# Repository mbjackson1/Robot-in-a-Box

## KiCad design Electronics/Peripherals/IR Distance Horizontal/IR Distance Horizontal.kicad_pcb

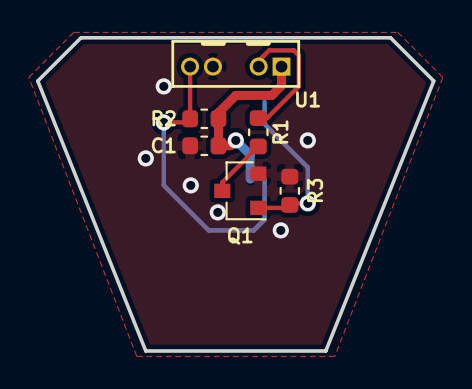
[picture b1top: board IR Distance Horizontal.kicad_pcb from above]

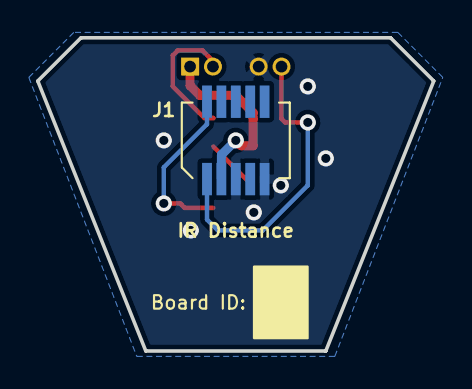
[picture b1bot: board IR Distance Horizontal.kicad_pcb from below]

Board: 2 copper layers, 22.0 x 17.4 mm, 9 parts (2 on the bottom side), 6 nets.

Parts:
C1: 100nF; C_0603_1608Metric
J1: Conn_01x10; Molex_SlimStack_533071071_2x05_P0.8mm_Vertical_Female
Q1: FDV303N; SOT-23
R1: 22R; R_0603_1608Metric
R2, R3: 10k; R_0603_1608Metric
T1: IR Distance; PCB_Title_&_Version
T2: Board ID; Board_Number
U1: TCRT1000; Vishay_TCRT10x0_Reflective_Sensor

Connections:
+3V3: C1.2, J1.3, R2.1, U1.1
/ANALOG: J1.1, R2.2, U1.4
/TIMER: J1.2, Q1.1, R3.2
GND: C1.1, J1.5, J1.9, Q1.2, R3.1, U1.3
unnamed: Q1.3, R1.1
unnamed: R1.2, U1.2

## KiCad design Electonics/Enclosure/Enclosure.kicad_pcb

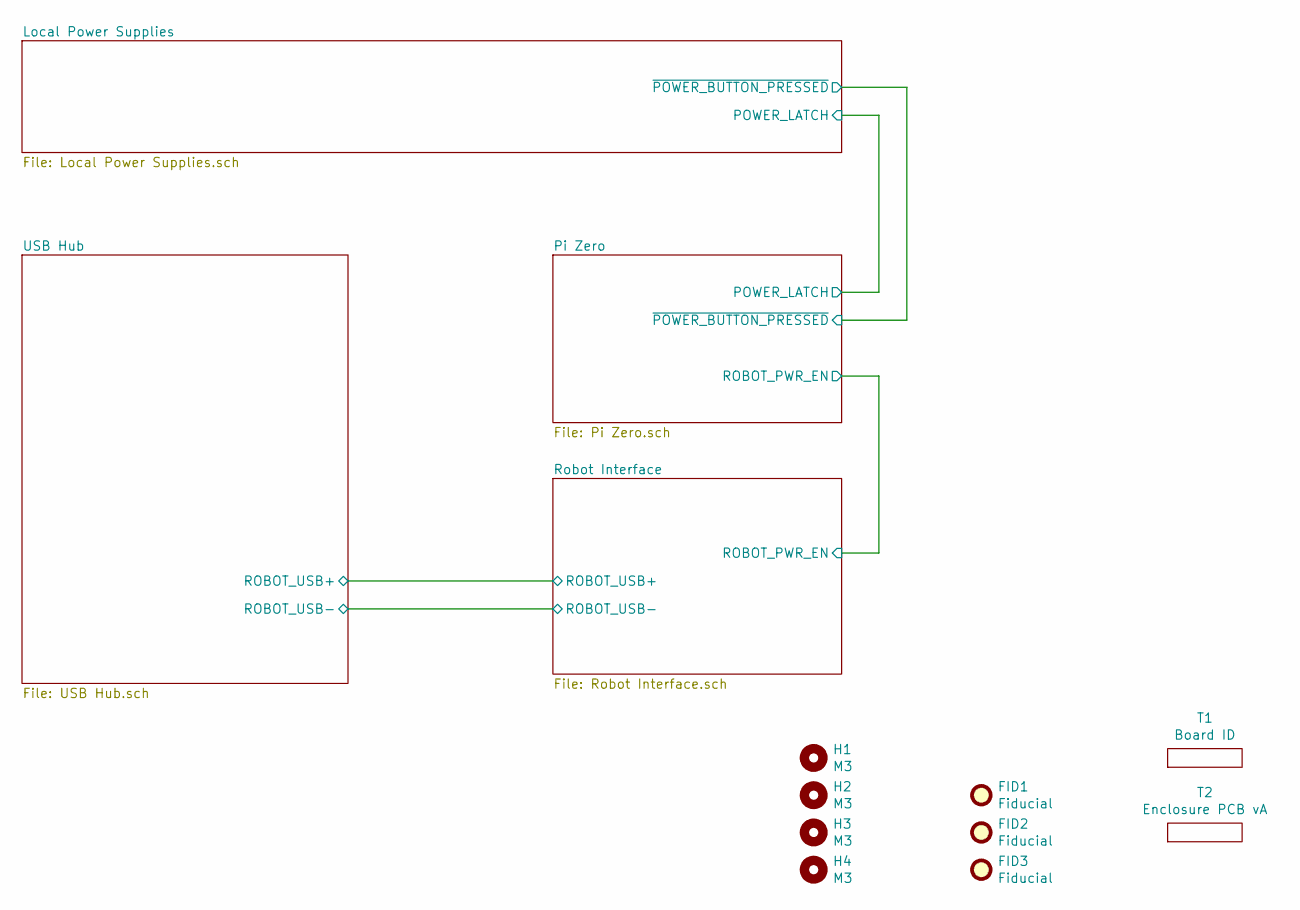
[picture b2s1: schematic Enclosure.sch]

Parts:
FID1, FID2, FID3: Fiducial; Fiducial_0.5mm_Mask1mm
H1, H2, H3, H4: M3; MountingHole_3.2mm_M3
T1: Board ID; Board_Number
T2: Enclosure PCB vA; PCB_Title_&_Version

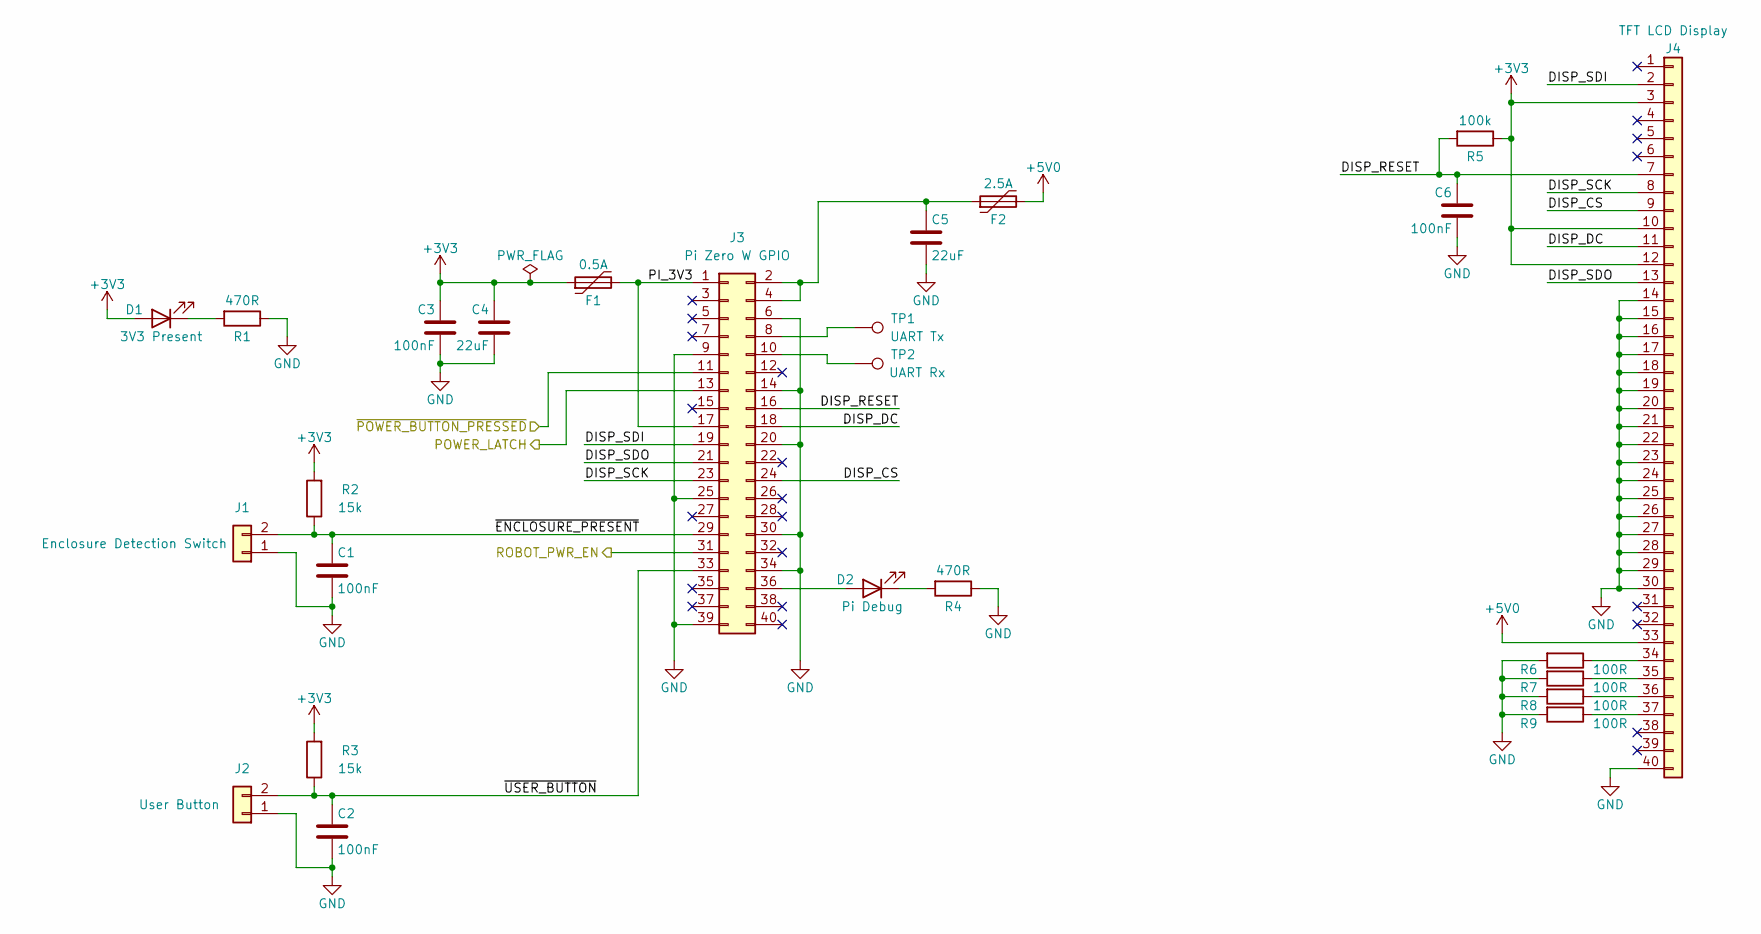
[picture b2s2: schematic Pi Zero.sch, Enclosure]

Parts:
C1, C2, C3, C6: 100nF; C_0603_1608Metric; Manufacturer Part Number CL10B104KB8NNNL; LCSC Part Number C14663
C4, C5: 22uF; C_1206_3216Metric; Manufacturer Part Number CL31B226MPHNNNE; LCSC Part Number C5672
D1, D2: LED; D_0603_1608Metric; Manufacturer Part Number 150060VS75000
F1: 0.5A; Fuse_1812_4532Metric; Manufacturer Part Number MF-MSMF050-2
F2: 2.5A; Fuse_1812_4532Metric; Manufacturer Part Number MF-MSMF250/16X-2
J1, J2: Conn_01x02; Molex_KK-254_AE-6410-02A_1x02_P2.54mm_Vertical; Manufacturer Part Number 0022232021
J3: 02x20 Header; Raspberry_Pi_Zero_Socketed_THT_FaceDown_MountingHoles; Manufacturer Part Number M20-7832046
J4: Conn_01x40; Hirose_FH12-40S-0.5SH_1x40-1MP_P0.50mm_Horizontal; Manufacturer Part Number FH12S-40S-0.5SH(55)
R1, R4: 470R; R_0603_1608Metric; Manufacturer Part Number RC0603FR-07470RL; LCSC Part Number C23179
R2, R3: 15k; R_0603_1608Metric; Manufacturer Part Number RC0603FR-0715KL; LCSC Part Number C22809
R5: 100k; R_0603_1608Metric; Manufacturer Part Number RC0603FR-07100KL; LCSC Part Number C25803
R6, R7, R8, R9: 100R; R_0603_1608Metric; Manufacturer Part Number RC0603FR-07100RL; LCSC Part Number C22775
TP1, TP2: TestPoint; TestPoint_Pad_1.5x1.5mm

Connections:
+3V3: C3.1, C4.1, D1.2 (A), F1.1, J4.3, J4.10, J4.12, R2.2, R3.2, R5.1; also elsewhere on the board
+5V: F2.2, J4.33; also elsewhere on the board
/Local Power Supplies/POWER_LATCH: J3.13; also elsewhere on the board
/Local Power Supplies/~POWER_BUTTON_PRESSED: J3.11; also elsewhere on the board
/Pi Zero/DISP_CS: J3.24, J4.9
/Pi Zero/DISP_DC: J3.18, J4.11
/Pi Zero/DISP_RESET: C6.1, J3.16, J4.7, R5.2
/Pi Zero/DISP_SCK: J3.23, J4.8
/Pi Zero/DISP_SDI: J3.19, J4.2
/Pi Zero/DISP_SDO: J3.21, J4.13
/Pi Zero/PI_3V3: F1.2, J3.1, J3.17
/Pi Zero/ROBOT_PWR_EN: J3.31; also elsewhere on the board
/Pi Zero/~ENCLOSURE_PRESENT: C1.1, J1.2, J3.29, R2.1
/Pi Zero/~USER_BUTTON: C2.1, J2.2, J3.33, R3.1
GND: C1.2, C2.2, C3.2, C4.2, C5.2, C6.2, J1.1, J2.1, J3.6, J3.9, J3.14, J3.20, J3.25, J3.30, J3.34, J3.39, J4.14, J4.15, J4.16, J4.17, J4.18, J4.19, J4.20, J4.21, J4.22, J4.23, J4.24, J4.25, J4.26, J4.27, J4.28, J4.29, J4.30, J4.40, R1.1, R4.1, R6.2, R7.2, R8.2, R9.2; also elsewhere on the board
unnamed: C5.1, F2.1, J3.2, J3.4
unnamed: D1.1 (K), R1.2
unnamed: D2.1 (K), R4.2
unnamed: D2.2 (A), J3.36
unnamed: J3.8, TP1.1
unnamed: J3.10, TP2.1
unnamed: J4.34, R6.1
unnamed: J4.35, R7.1
unnamed: J4.36, R8.1
unnamed: J4.37, R9.1

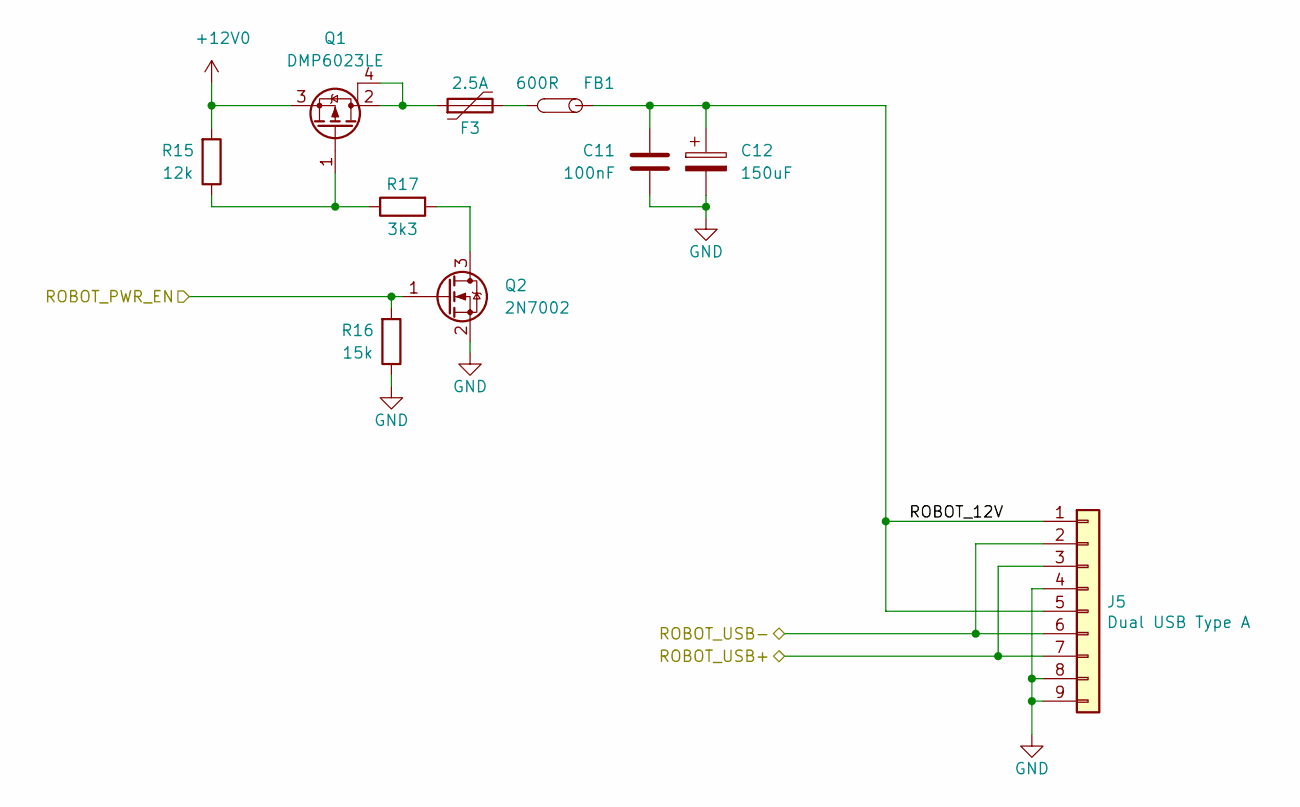
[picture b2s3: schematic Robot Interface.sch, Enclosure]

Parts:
C11: 100nF; C_0603_1608Metric; Manufacturer Part Number CL10B104KB8NNNL; LCSC Part Number C14663
C12: 150uF; CP_Elec_6.3x7.7; Manufacturer Part Number EEE-FKC151XAP
F3: 2.5A; Fuse_1812_4532Metric; Manufacturer Part Number MF-MSMF250/16X-2
FB1: 600R; L_1206_3216Metric; Manufacturer Part Number 742792118; LCSC Part Number C74090
J5: Dual USB Type A; USB_A_Wuerth_61400826021_Horizontal_Stacked; Manufacturer Part Number 61400826021
Q1: DMP6023LE; SOT-223; Manufacturer Part Number DMP6023LE-13; LCSC Part Number C154901
Q2: 2N7002; SOT-23; Manufacturer Part Number 2N7002P,235; LCSC Part Number C65189
R15: 12k; R_0603_1608Metric; Manufacturer Part Number RC0603FR-0712KL; LCSC Part Number C22790
R16: 15k; R_0603_1608Metric; Manufacturer Part Number RC0603FR-0715KL; LCSC Part Number C22809
R17: 3k3; R_0603_1608Metric; Manufacturer Part Number RC0603FR-073K3L; LCSC Part Number C22978

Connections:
+12V: Q1.3 (S), R15.2; also elsewhere on the board
/Pi Zero/ROBOT_PWR_EN: Q2.1 (G), R16.2; also elsewhere on the board
/Robot Interface/ROBOT_12V: C11.1, C12.1, FB1.1, J5.1, J5.5
/Robot Interface/ROBOT_USB+: J5.3, J5.7; also elsewhere on the board
/Robot Interface/ROBOT_USB-: J5.2, J5.6; also elsewhere on the board
GND: C11.2, C12.2, J5.4, J5.8, J5.9, Q2.2 (S), R16.1; also elsewhere on the board
unnamed: F3.1, Q1.2 (D), Q1.4 (D)
unnamed: F3.2, FB1.2
unnamed: Q1.1 (G), R15.1, R17.1
unnamed: Q2.3 (D), R17.2

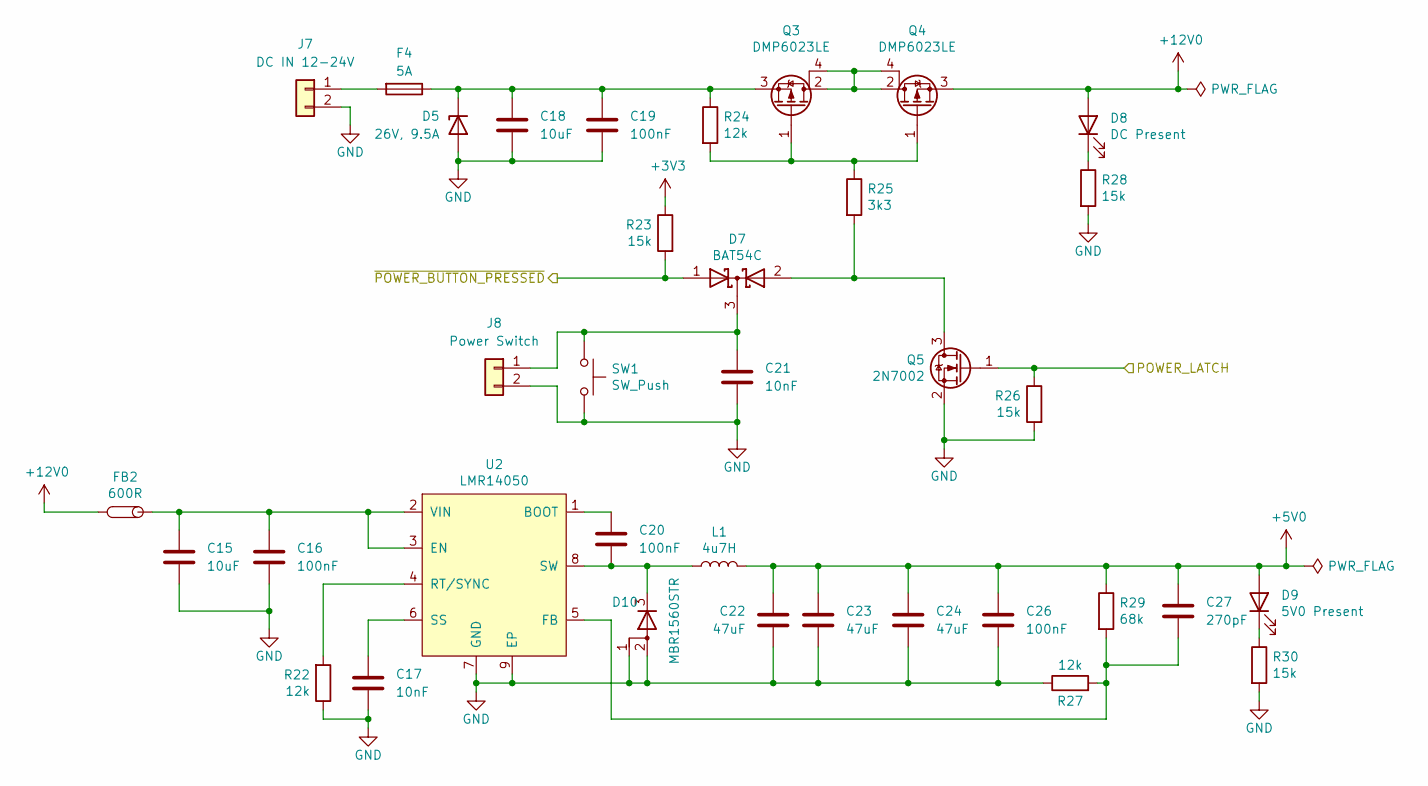
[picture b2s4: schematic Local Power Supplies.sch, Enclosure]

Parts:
C15, C18: 10uF; C_1210_3225Metric; Manufacturer Part Number CL32B106KBJNNWE; LCSC Part Number C380537
C16, C19, C20, C26: 100nF; C_0603_1608Metric; Manufacturer Part Number CL10B104KB8NNNL; LCSC Part Number C14663
C17, C21: 10nF; C_0603_1608Metric; Manufacturer Part Number CL10B103KB8NNNC; LCSC Part Number C1589
C22, C23, C24: 47uF; C_1206_3216Metric; Manufacturer Part Number CL31A476MPHNNNE; LCSC Part Number C96123
C27: 270pF; C_0603_1608Metric; Manufacturer Part Number CL10C271JB81PNC; LCSC Part Number C1657
D5: 26V, 9.5A; D_SMA; Manufacturer Part Number SMAJ26A; LCSC Part Number C134975
D7: BAT54C; SOT-23; Manufacturer Part Number BAT54C,215; LCSC Part Number C37704
D8, D9: LED; D_0603_1608Metric; Manufacturer Part Number 150060VS75000
D10: MBR1560STR; TO-277B; Manufacturer Part Number MBR1560STR; LCSC Part Number C305422
F4: 5A; Fuseholder_Littelfuse_154; Manufacturer Part Number 0154005.DR
FB2: 600R; L_1206_3216Metric; Manufacturer Part Number 742792118; LCSC Part Number C74090
J7, J8: Conn_01x02; Molex_KK-254_AE-6410-02A_1x02_P2.54mm_Vertical; Manufacturer Part Number 0022232021
L1: 4u7H; L_Bourns_SRR1210A; Manufacturer Part Number SRR1210A-4R7Y
Q3, Q4: DMP6023LE; SOT-223; Manufacturer Part Number DMP6023LE-13; LCSC Part Number C154901
Q5: 2N7002; SOT-23; Manufacturer Part Number 2N7002P,235; LCSC Part Number C65189
R22, R24, R27: 12k; R_0603_1608Metric; Manufacturer Part Number RC0603FR-0712KL; LCSC Part Number C22790
R23, R26, R28, R30: 15k; R_0603_1608Metric; Manufacturer Part Number RC0603FR-0715KL; LCSC Part Number C22809
R25: 3k3; R_0603_1608Metric; Manufacturer Part Number RC0603FR-073K3L; LCSC Part Number C22978
R29: 68k; R_0603_1608Metric; Manufacturer Part Number RC0603FR-0768KL; LCSC Part Number C23231
SW1: SW_Push; SW_SPST_Omron_B3FS-100xP; Manufacturer Part Number B3FS-1000P
U2: LMR14050; SOIC-8-1EP_3.9x4.9mm_P1.27mm_EP2.41x3.3mm_ThermalVias; Manufacturer Part Number LMR14050SDDAR; LCSC Part Number C155484

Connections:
+3V3: R23.1; also elsewhere on the board
+5V: C22.1, C23.1, C24.1, C26.1, C27.1, D9.2 (A), L1.2, R29.1; also elsewhere on the board
+12V: D8.2 (A), FB2.2, Q4.3 (S); also elsewhere on the board
/Local Power Supplies/POWER_LATCH: Q5.1 (G), R26.1; also elsewhere on the board
/Local Power Supplies/~POWER_BUTTON_PRESSED: D7.1 (A), R23.2; also elsewhere on the board
GND: C15.2, C16.2, C17.2, C18.2, C19.2, C21.2, C22.2, C23.2, C24.2, C26.2, D5.2 (A), D10.1 (A), D10.2 (A), J7.2, J8.2, Q5.2 (S), R22.1, R26.2, R27.1, R28.2, R30.2, SW1.1, U2.7 (GND), U2.9 (EP); also elsewhere on the board
unnamed: C15.1, C16.1, FB2.1, U2.2 (VIN), U2.3 (EN)
unnamed: C17.1, U2.6 (SS)
unnamed: C18.1, C19.1, D5.1 (K), F4.1, Q3.3 (S), R24.1
unnamed: C20.1, U2.1 (BOOT)
unnamed: C20.2, D10.3 (K), L1.1, U2.8 (SW)
unnamed: C21.1, D7.3 (K), J8.1, SW1.2
unnamed: C27.2, R27.2, R29.2, U2.5 (FB)
unnamed: D7.2 (A), Q5.3 (D), R25.2
unnamed: D8.1 (K), R28.1
unnamed: D9.1 (K), R30.1
unnamed: F4.2, J7.1
unnamed: Q3.1 (G), Q4.1 (G), R24.2, R25.1
unnamed: Q3.2 (D), Q3.4 (D), Q4.2 (D), Q4.4 (D)
unnamed: R22.2, U2.4 (RT/SYNC)

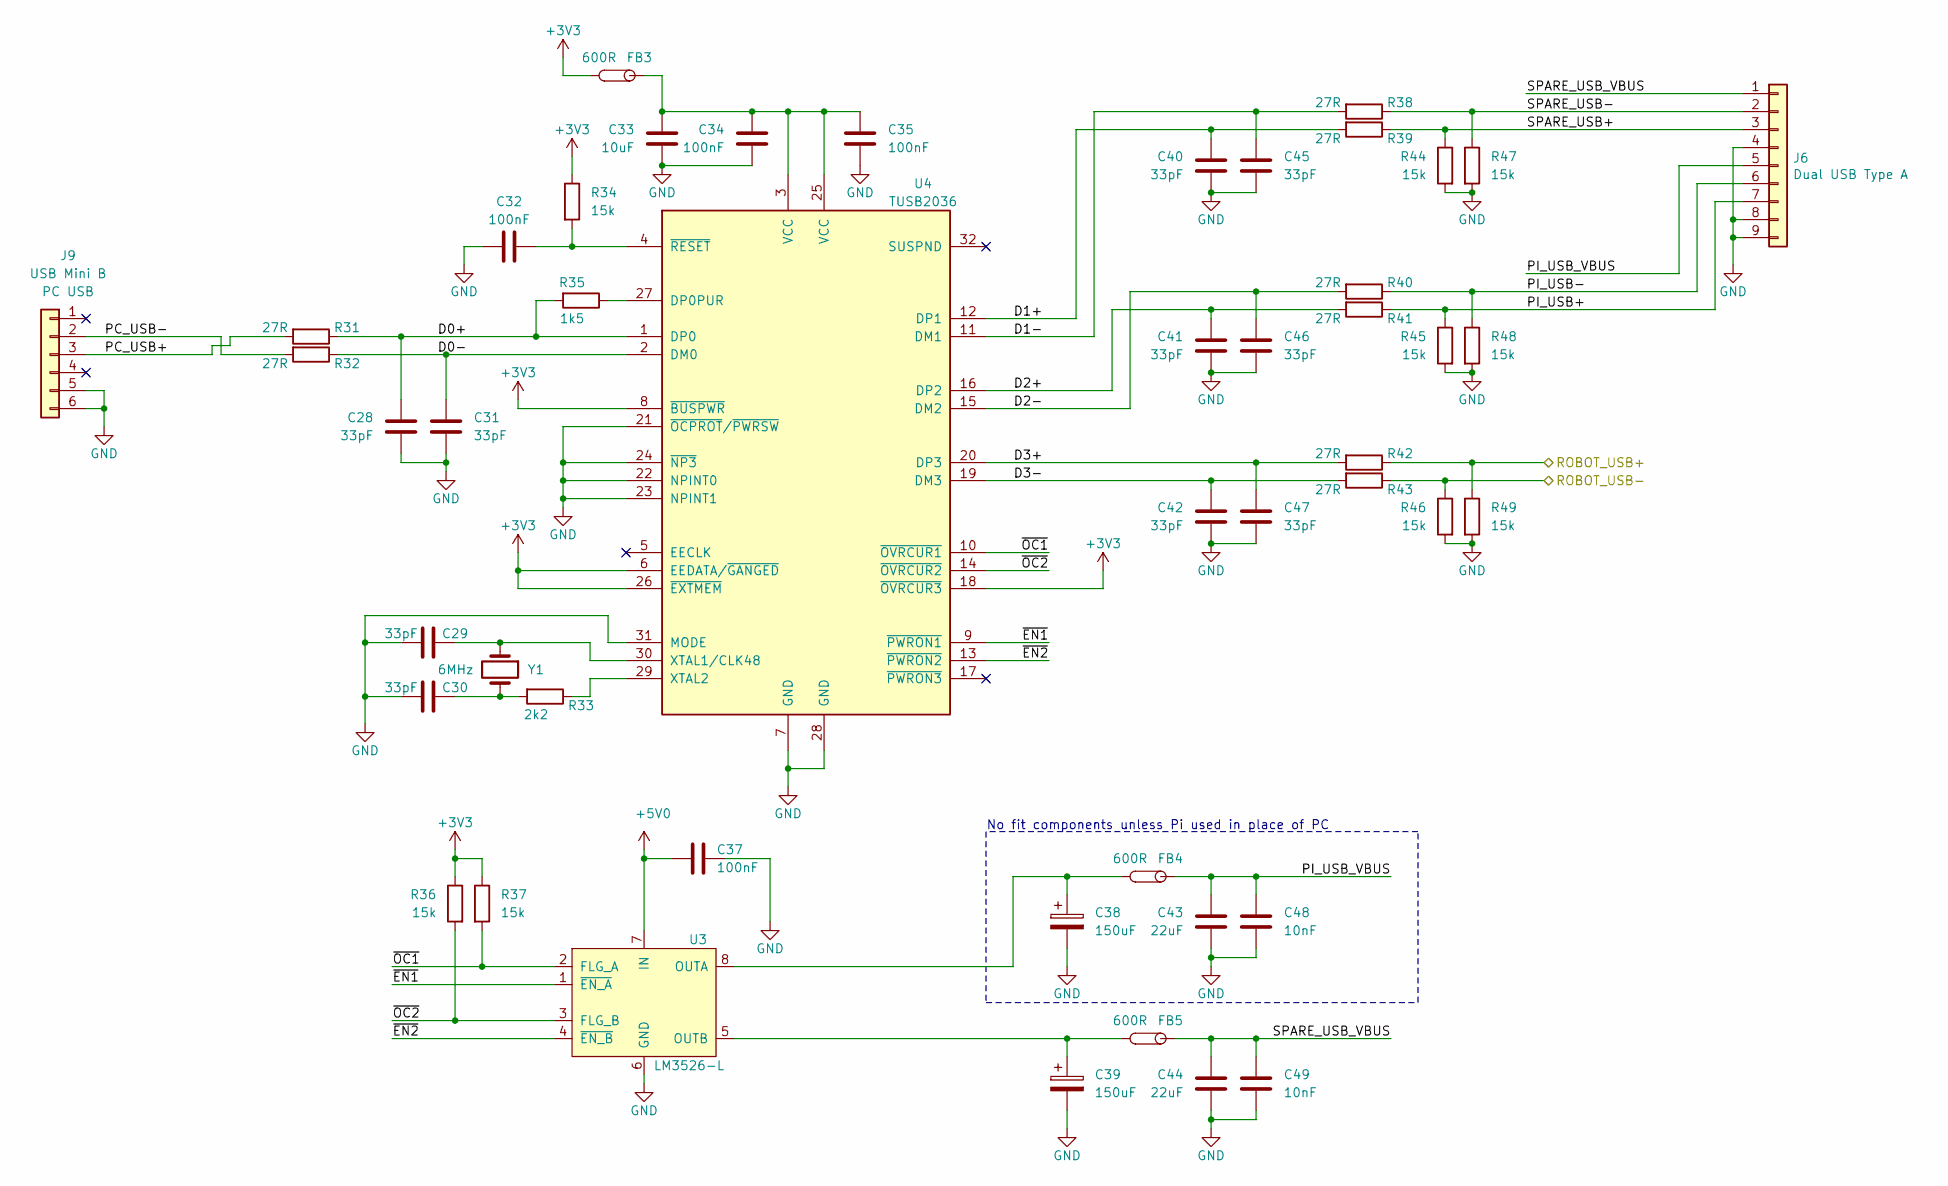
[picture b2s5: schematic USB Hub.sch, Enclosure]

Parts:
C28, C29, C30, C31, C40, C41, C42, C45, C46, C47: 33pF; C_0603_1608Metric; Manufacturer Part Number CL10C330JB8NNNC; LCSC Part Number C1663
C32, C34, C35, C37: 100nF; C_0603_1608Metric; Manufacturer Part Number CL10B104KB8NNNL; LCSC Part Number C14663
C33: 10uF; C_1210_3225Metric; Manufacturer Part Number CL32B106KBJNNWE; LCSC Part Number C380537
C38, C39: 150uF; CP_Elec_6.3x7.7; Manufacturer Part Number EEE-FKC151XAP
C43, C44: 22uF; C_1206_3216Metric; Manufacturer Part Number CL31B226MPHNNNE; LCSC Part Number C5672
C48, C49: 10nF; C_0603_1608Metric; Manufacturer Part Number CL10B103KB8NNNC; LCSC Part Number C1589
FB3, FB4, FB5: 600R; L_1206_3216Metric; Manufacturer Part Number 742792118; LCSC Part Number C74090
J6: Dual USB Type A; USB_A_Wuerth_61400826021_Horizontal_Stacked; Manufacturer Part Number 61400826021
J9: USB Mini B; USB_Micro-B_Wuerth_629105150521; Manufacturer Part Number 629105150521
R31, R32, R38, R39, R40, R41, R42, R43: 27R; R_0603_1608Metric; Manufacturer Part Number RC0603FR-0727RL; LCSC Part Number C25190
R33: 2k2; R_0603_1608Metric; Manufacturer Part Number RC0603FR-072K2L; LCSC Part Number C4190
R34, R36, R37, R44, R45, R46, R47, R48, R49: 15k; R_0603_1608Metric; Manufacturer Part Number RC0603FR-0715KL; LCSC Part Number C22809
R35: 1k5; R_0603_1608Metric; Manufacturer Part Number RC0603FR-071K5L; LCSC Part Number C22843
U3: LM3526-L; SOIC-8_3.9x4.9mm_P1.27mm; Manufacturer Part Number LM3526MX-L/NOPB
U4: TUSB2036; LQFP-32_7x7mm_P0.8mm; Manufacturer Part Number TUSB2036VFR
Y1: 6MHz; Crystal_SMD_HC49-SD; Manufacturer Part Number HC49USM-FF3F18-6.000MHZ

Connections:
+3V3: FB3.2, R34.1, R36.1, R37.1, U4.6 (EEDATA/~GANGED), U4.8 (~BUSPWR), U4.18 (~OVRCUR3), U4.26 (~EXTMEM); also elsewhere on the board
+5V: C37.2, U3.7 (IN); also elsewhere on the board
/Robot Interface/ROBOT_USB+: R42.1, R49.1; also elsewhere on the board
/Robot Interface/ROBOT_USB-: R43.1, R46.1; also elsewhere on the board
/USB Hub/D0+: C28.1, R31.1, R35.2, U4.1 (DP0)
/USB Hub/D0-: C31.1, R32.1, U4.2 (DM0)
/USB Hub/D1+: C40.1, R39.2, U4.12 (DP1)
/USB Hub/D1-: C45.1, R38.2, U4.11 (DM1)
/USB Hub/D2+: C41.1, R41.2, U4.16 (DP2)
/USB Hub/D2-: C46.1, R40.2, U4.15 (DM2)
/USB Hub/D3+: C47.1, R42.2, U4.20 (DP3)
/USB Hub/D3-: C42.1, R43.2, U4.19 (DM3)
/USB Hub/PC_USB+: J9.3, R31.2
/USB Hub/PC_USB-: J9.2, R32.2
/USB Hub/PI_USB+: J6.7, R41.1, R45.1
/USB Hub/PI_USB-: J6.6, R40.1, R48.1
/USB Hub/PI_USB_VBUS: C43.1, C48.1, FB4.1, J6.5
/USB Hub/SPARE_USB+: J6.3, R39.1, R44.1
/USB Hub/SPARE_USB-: J6.2, R38.1, R47.1
/USB Hub/SPARE_USB_VBUS: C44.1, C49.1, FB5.1, J6.1
/USB Hub/~EN1: U3.1 (~EN_A), U4.9 (~PWRON1)
/USB Hub/~EN2: U3.4 (~EN_B), U4.13 (~PWRON2)
/USB Hub/~OC1: R37.2, U3.2 (FLG_A), U4.10 (~OVRCUR1)
/USB Hub/~OC2: R36.2, U3.3 (FLG_B), U4.14 (~OVRCUR2)
GND: C28.2, C29.2, C30.2, C31.2, C32.2, C33.2, C34.2, C35.2, C37.1, C38.2, C39.2, C40.2, C41.2, C42.2, C43.2, C44.2, C45.2, C46.2, C47.2, C48.2, C49.2, J6.4, J6.8, J6.9, J9.5, J9.6, R44.2, R45.2, R46.2, R47.2, R48.2, R49.2, U3.6 (GND), U4.7 (GND), U4.21 (~OCPROT~/~PWRSW~), U4.22 (NPINT0), U4.23 (NPINT1), U4.24 (~NP3), U4.28 (GND), U4.31 (MODE); also elsewhere on the board
unnamed: C29.1, U4.30 (XTAL1/CLK48), Y1.1
unnamed: C30.1, R33.2, Y1.2
unnamed: C32.1, R34.2, U4.4 (~RESET)
unnamed: C33.1, C34.1, C35.1, FB3.1, U4.3 (VCC), U4.25 (VCC)
unnamed: C38.1, FB4.2, U3.8 (OUTA)
unnamed: C39.1, FB5.2, U3.5 (OUTB)
unnamed: R33.1, U4.29 (XTAL2)
unnamed: R35.1, U4.27 (DP0PUR)

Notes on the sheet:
No fit components unless Pi used in place of PC

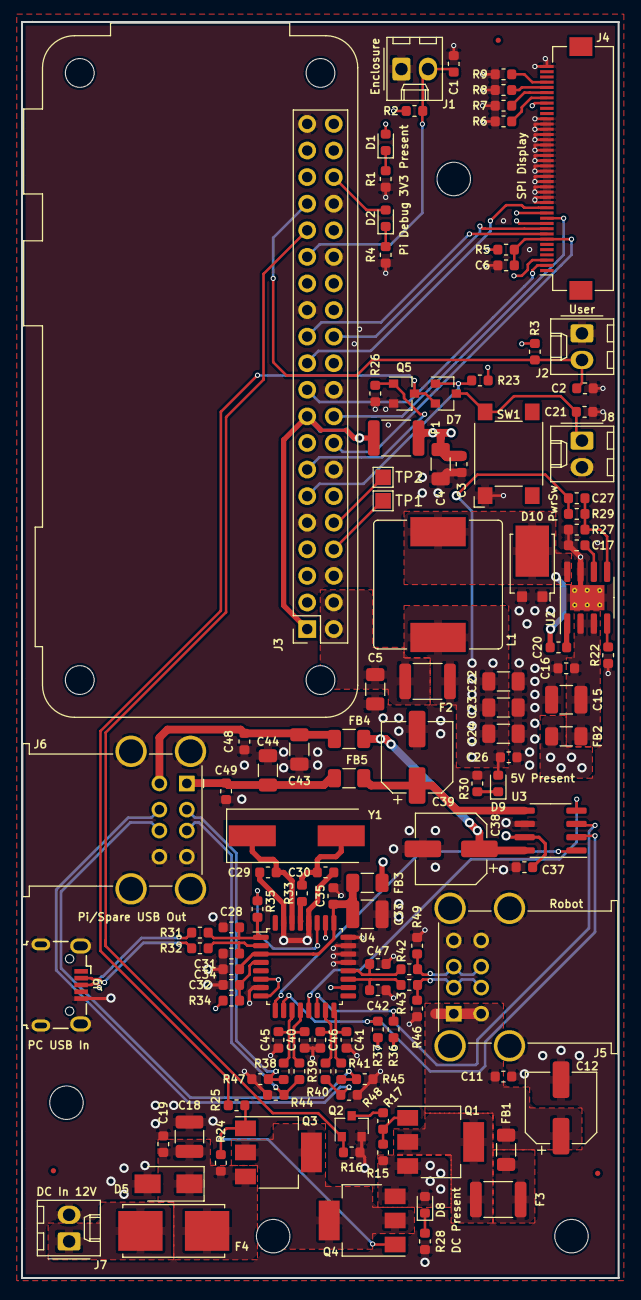
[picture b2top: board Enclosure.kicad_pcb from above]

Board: 4 copper layers, 57.0 x 120.0 mm, 128 parts (1 on the bottom side), 75 nets.

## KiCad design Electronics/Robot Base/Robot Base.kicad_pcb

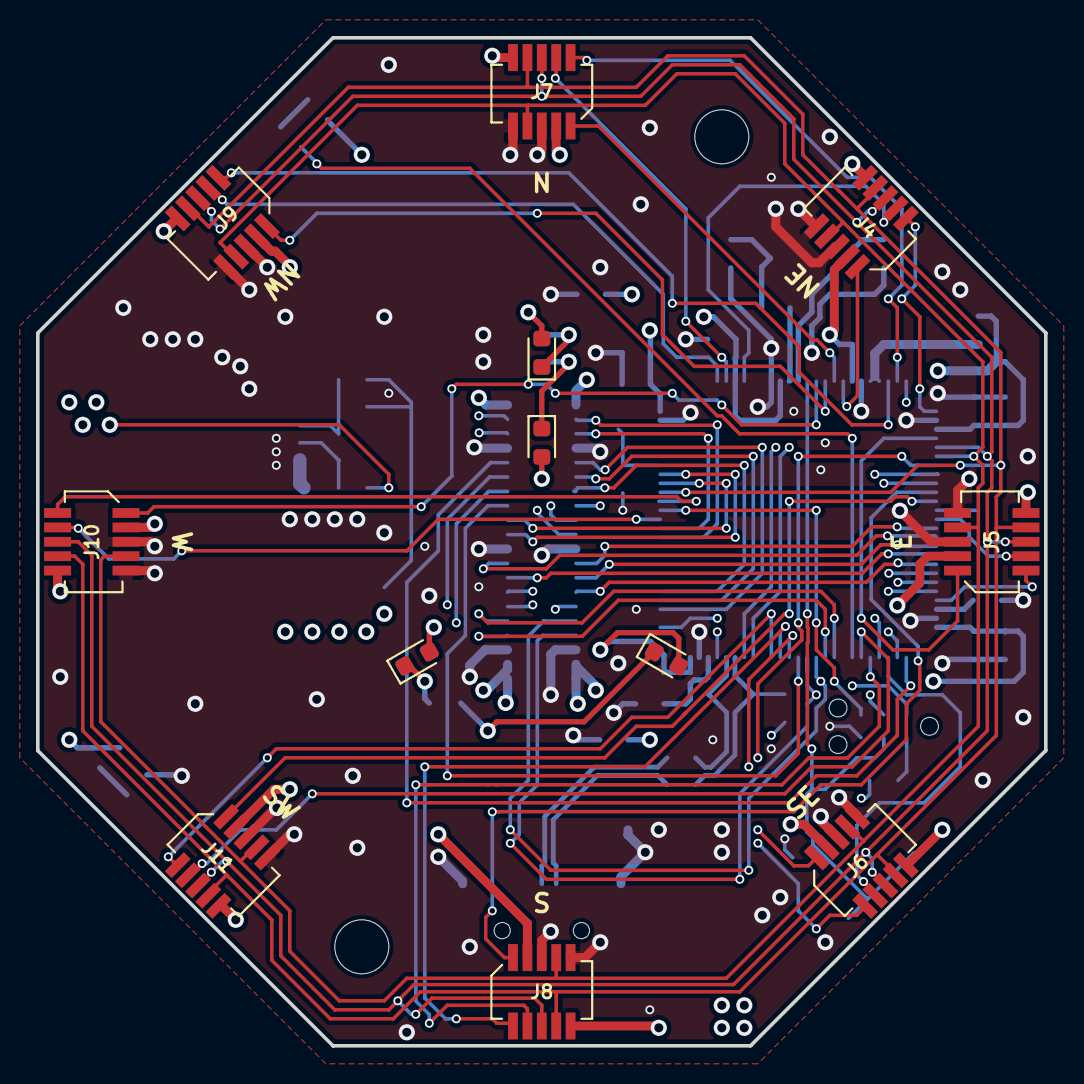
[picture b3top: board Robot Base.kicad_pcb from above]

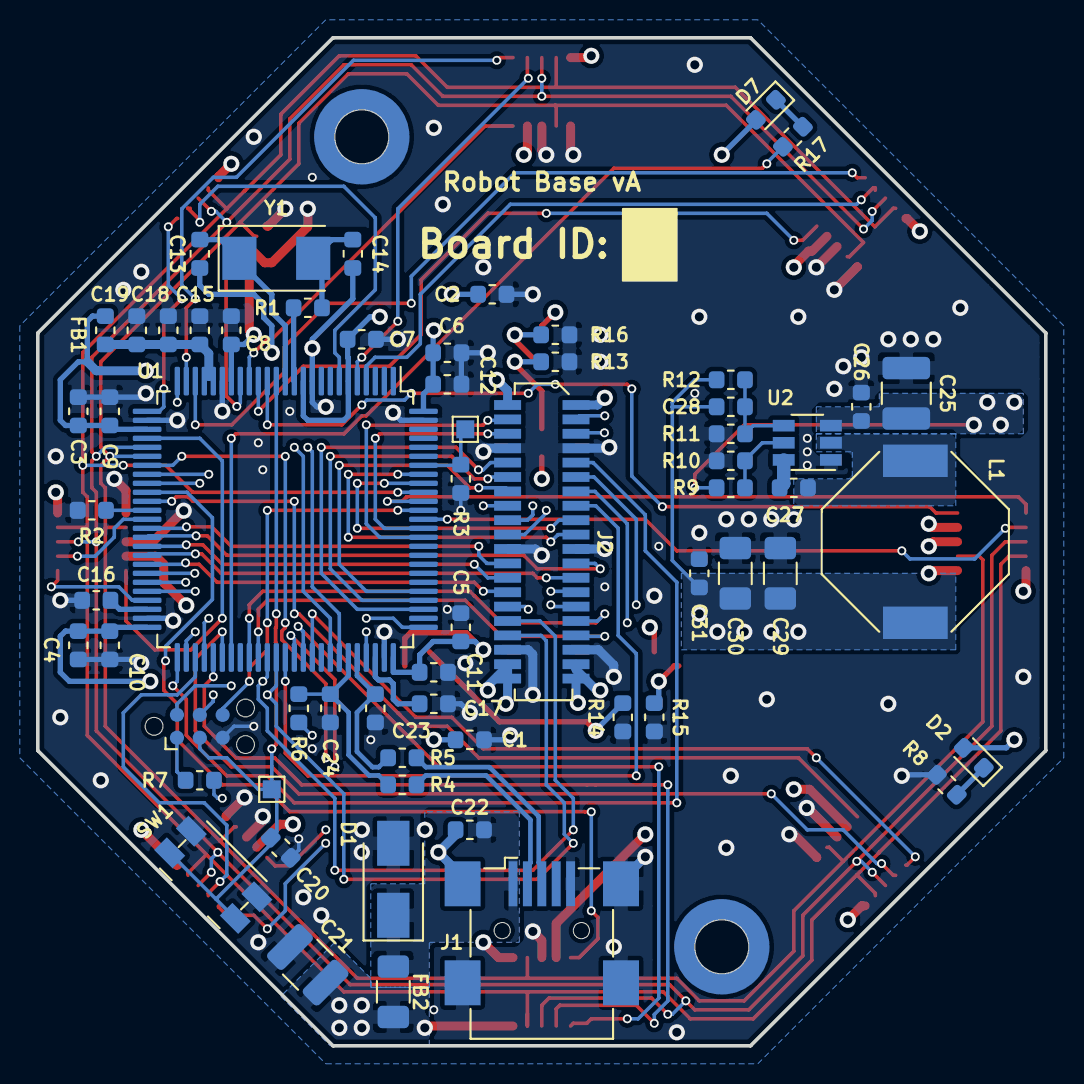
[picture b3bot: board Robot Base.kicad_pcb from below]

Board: 4 copper layers, 56.0 x 56.0 mm, 79 parts (66 on the bottom side), 87 nets.

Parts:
C1, C2, C16, C17: 2u2F; C_0603_1608Metric
C3, C4, C5, C6, C19: 1uF; C_0603_1608Metric
C7, C8, C9, C10, C11, C12, C18, C20, C22, C26, C27, C31: 100nF; C_0603_1608Metric
C13, C14, C23, C24: 33pF; C_0603_1608Metric
C15: 10nF; C_0603_1608Metric
C21, C25: 10uF; C_1210_3225Metric
C28: 56pF; R_0603_1608Metric
C29, C30: 22uF; C_1206_3216Metric
D1: 26V, 9.5A; D_SMA
D2: Green LED; LED_0603_1608Metric
D3, D4, D5, D6, D7: Red LED; LED_0603_1608Metric
FB1: 1k, 600mA; L_0603_1608Metric
FB2: 600R; L_1206_3216Metric
H1, H2: MountingHole; Mounting_Wuerth_WA-SMSI-M2_H4.5mm_9774045243
J1: Conn_01x05_Shielded; USB_Mini-B_Wuerth_65100516121_Horizontal
J2: SlimStack 0.8mm 2x20; Molex_SlimStack_524654071_2x20_P0.8mm_Vertical
J3: Tag Connect; Tag-Connect_TC2030-IDC-NL_2x03_P1.27mm_Vertical
J4, J5, J6, J7, J8, J9, J10, J11: SlimStack 0.8mm 2x05; Molex_SlimStack_524651071_2x05_P0.8mm_Vertical
L1: 10uH, 3.6A; L_Bourns-SRU1028_10.0x10.0mm
R1, R7: 0R; R_0603_1608Metric
R2, R3, R8: 10k; R_0603_1608Metric
R4, R5: 27R; R_0603_1608Metric
R6: 1k5; R_0603_1608Metric
R9: 470k; R_0603_1608Metric
R10: 68k; R_0603_1608Metric
R11: 22k; R_0603_1608Metric
R12: 100k; R_0603_1608Metric
R13, R14, R15, R16, R17: 220R; R_0603_1608Metric
SW1: SW_Push; Panasonic_EVQPUK_EVQPUB
T1: Robot Base vA; PCB_Title_&_Version
T2: Board ID; Board_Number
TP1: NRST; TestPoint_Pad_1.0x1.0mm
TP2: BOOT0; TestPoint_Pad_1.0x1.0mm
U1: STM32F401VCT6; LQFP-100_14x14mm_P0.5mm
U2: TPS54202; TSOT-23-6
Y1: 25MHz; Crystal_SMD_Abracon_ABM3-2Pin_5.0x3.2mm

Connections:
+3V3: C1.1, C2.1, C3.1, C4.1, C5.1, C6.1, C7.1, C8.1, C9.1, C10.1, C11.1, C12.1, C28.1, C29.2, C30.2, C31.2, D3.2, D4.2, D5.2, D6.2, D7.2, FB1.1, J2.1, J2.2, J4.3, J5.3, J6.3, J7.3, J8.3, J9.3, J10.3, J11.3, L1.2, R6.1, R7.2, R12.2, U1.6, U1.11, U1.19, U1.28, U1.50, U1.75, U1.100
+12V: C21.2, C25.2, C26.2, D2.2, FB2.1, J2.37, J2.38, J2.39, J2.40, J4.10, J5.10, J6.10, J7.10, J8.10, J9.10, J10.10, J11.10, R9.1, U2.3
/Peripheral Connectors/PA0: J9.2, U1.23
/Peripheral Connectors/PA1: J7.2, U1.24
/Peripheral Connectors/PA3: J4.2, U1.26
/Peripheral Connectors/PA4: J5.1, U1.29
/Peripheral Connectors/PA7: J6.1, U1.32
/Peripheral Connectors/PB0: J8.1, U1.35
/Peripheral Connectors/PB1: J11.1, U1.36
/Peripheral Connectors/PB4: J10.2, U1.90
/Peripheral Connectors/PB10: J5.2, U1.47
/Peripheral Connectors/PB14: J6.4, U1.53
/Peripheral Connectors/PC0: J10.1, U1.15
/Peripheral Connectors/PC1: J9.1, U1.16
/Peripheral Connectors/PC2: J7.1, U1.17
/Peripheral Connectors/PC3: J4.1, U1.18
/Peripheral Connectors/PC7: J6.2, U1.64
/Peripheral Connectors/PC8: J8.2, U1.65
/Peripheral Connectors/PC9: J11.2, U1.66
/Peripheral Connectors/PC13: J4.4, U1.7
/Peripheral Connectors/PD7: J10.4, U1.88
/Peripheral Connectors/PD8: J8.4, U1.55
/Peripheral Connectors/PD9: J11.4, U1.56
/Peripheral Connectors/PD10: R17.2, U1.57
/Peripheral Connectors/PE5: J9.4, U1.4
/Peripheral Connectors/PE6: J7.4, U1.5
/Peripheral Connectors/PE7: J5.4, U1.38
/Peripheral Connectors/SPI_MISO: J4.7, J5.7, J6.7, J7.7, J8.7, J9.7, J10.7, J11.7, U1.31
/Peripheral Connectors/SPI_MOSI: J4.8, J5.8, J6.8, J7.8, J8.8, J9.8, J10.8, J11.8, U1.91
/Peripheral Connectors/SPI_SCK: J4.6, J5.6, J6.6, J7.6, J8.6, J9.6, J10.6, J11.6, U1.30
/Processor/BOOT0: R3.2, TP2.1, U1.94
/Processor/NRST: C20.2, J3.3, SW1.1, TP1.1, U1.14
/Processor/PA2: J2.16, U1.25
/Processor/PA9: J2.3, U1.68
/Processor/PA10: J2.5, U1.69
/Processor/PB6: J2.17, U1.92
/Processor/PB7: J2.19, U1.93
/Processor/PB12: J2.9, U1.51
/Processor/PB13: J2.11, U1.52
/Processor/PB15: J2.13, U1.54
/Processor/PC4: J2.18, U1.33
/Processor/PC5: J2.20, U1.34
/Processor/PC6: J2.15, U1.63
/Processor/PC10: J2.10, U1.78
/Processor/PC11: J2.12, U1.79
/Processor/PC12: J2.14, U1.80
/Processor/PD5: J2.4, U1.86
/Processor/PD6: J2.6, U1.87
/Processor/PD12: J2.31, U1.59
/Processor/PD13: J2.33, U1.60
/Processor/PD14: J2.32, U1.61
/Processor/PD15: J2.34, U1.62
/Processor/PE8: J2.24, U1.39
/Processor/PE9: J2.23, U1.40
/Processor/PE10: J2.26, U1.41
/Processor/PE11: J2.25, U1.42
/Processor/PE12: J2.28, U1.43
/Processor/PE13: J2.27, U1.44
/Processor/PE14: J2.29, U1.45
/Processor/PE15: J2.30, U1.46
/Processor/STM_USB+: C23.2, R5.2, U1.71
/Processor/STM_USB-: C24.2, R4.1, R6.2, U1.70
/Processor/SWCLK: J3.4, U1.76
/Processor/SWDIO: J3.2, U1.72
/Processor/SWO: J3.6, U1.89
/Processor/USB+: J1.3, R5.1
/Processor/USB-: J1.2, R4.2
/Processor/VREF+: C15.1, C18.1, C19.1, FB1.2, U1.21, U1.22
GND: C1.2, C2.2, C3.2, C4.2, C5.2, C6.2, C7.2, C8.2, C9.2, C10.2, C11.2, C12.2, C13.2, C14.1, C15.2, C16.1, C17.1, C18.2, C19.2, C20.1, C21.1, C22.1, C23.1, C24.1, C25.1, C26.1, C29.1, C30.1, C31.1, D1.2, J1.5, J1.6, J2.7, J2.8, J2.21, J2.22, J2.35, J2.36, J3.5, J4.5, J4.9, J5.5, J5.9, J6.5, J6.9, J7.5, J7.9, J8.5, J8.9, J9.5, J9.9, J10.5, J10.9, J11.5, J11.9, R2.2, R3.1, R8.2, R10.2, R11.2, R13.2, R14.2, R15.2, R16.2, SW1.2, U1.10, U1.20, U1.27, U1.49, U1.74, U1.99, U2.1
unnamed: C13.1, U1.13, Y1.1
unnamed: C14.2, R1.1, Y1.2
unnamed: C16.2, U1.48
unnamed: C17.2, U1.73
unnamed: C22.2, D1.1, FB2.2, J1.1
unnamed: C27.1, U2.6
unnamed: C27.2, L1.1, U2.2
unnamed: C28.2, R11.1, R12.1, U2.4
unnamed: D2.1, R8.1
unnamed: D3.1, R13.1
unnamed: D4.1, R14.1
unnamed: D5.1, R15.1
unnamed: D6.1, R16.1
unnamed: D7.1, R17.1
unnamed: J3.1, R7.1
unnamed: R1.2, U1.12
unnamed: R2.1, U1.37
unnamed: R9.2, R10.1, U2.5
